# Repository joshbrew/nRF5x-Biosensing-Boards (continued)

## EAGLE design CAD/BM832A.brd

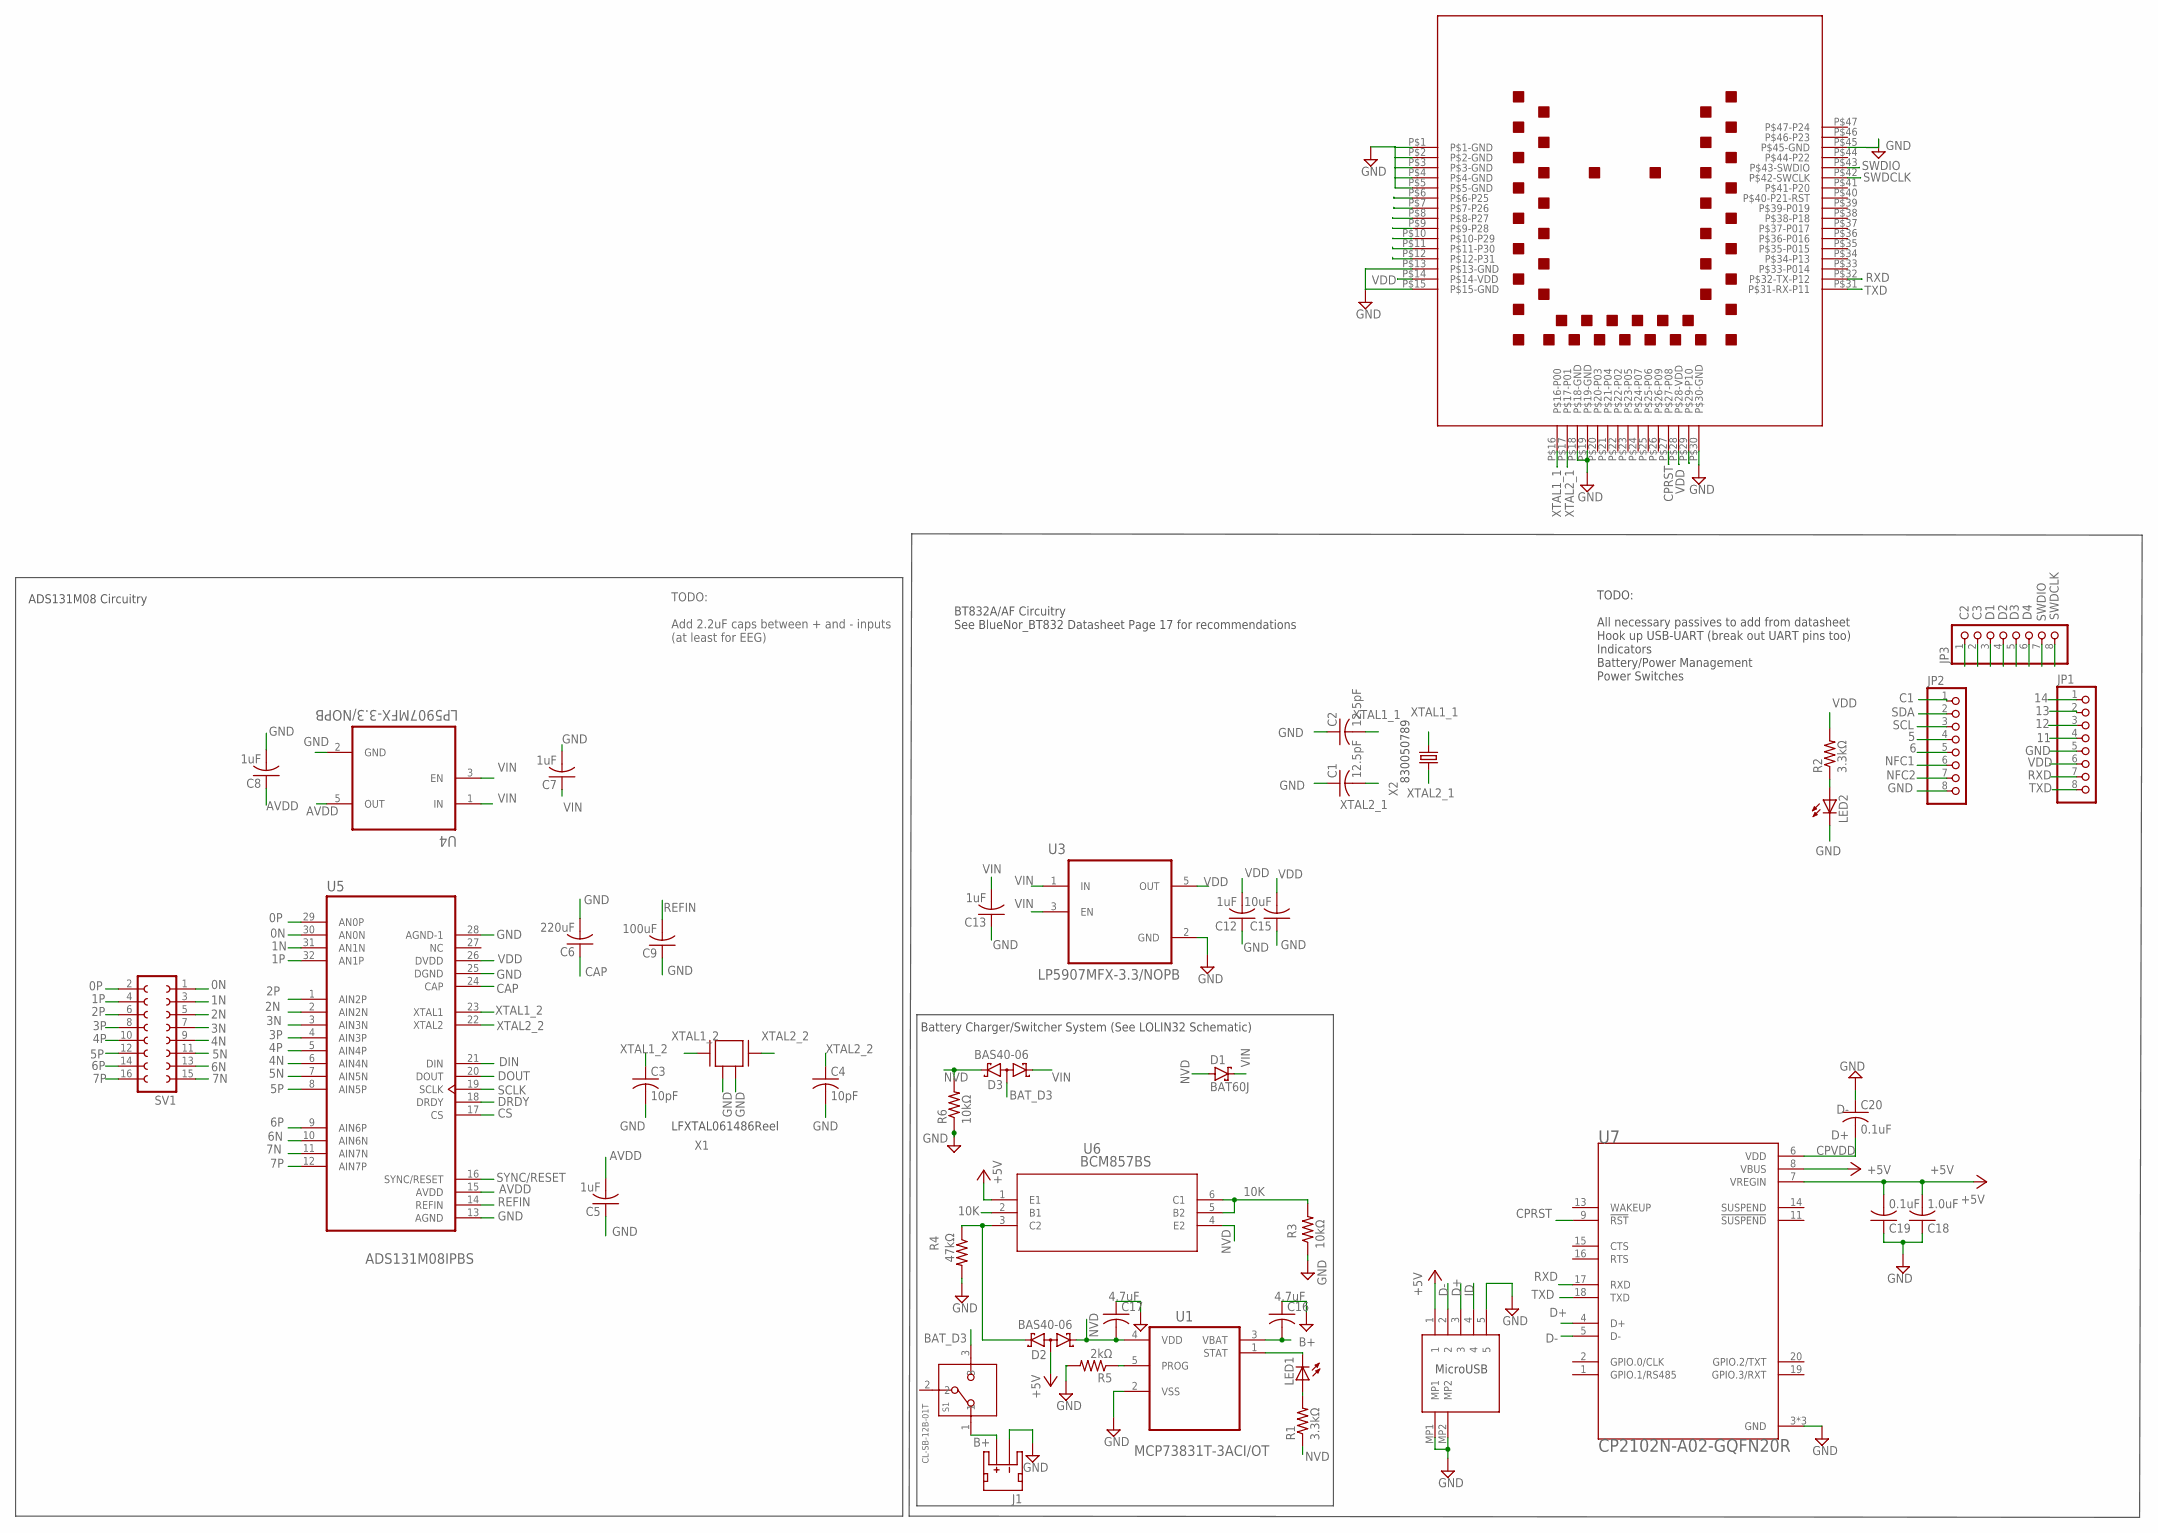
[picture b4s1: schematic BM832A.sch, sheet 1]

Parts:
C1, C2: 12.5pF; C0402
C3, C4: 10pF; C0402
C5, C7, C8, C12, C13: 1uF; C0402
C6: 220uF; C0402
C9: 100uF; C0402
C15: 10uF; C0402
C16, C17: 4.7uF; C0402
C18: 1.0uF; C0402
C19, C20: 0.1uF; C0402
D1: BAT60J; SOD323_ST
D2, D3: BAS40-06; SOT23
J1: JST_2MM_MALE; JST-2-SMD
JP1, JP2, JP3: PINHD-1X8CLEANBIG; 1X08-CLEANBIG
LED1, LED2: LEDCHIP-LED0603; CHIP-LED0603
R1, R2: 3.3kΩ; R0402
R3, R6: 10kΩ; R0402
R4: 47kΩ; R0402
R5: 2kΩ; R0402
S1: CL-SB-12B-01T; CL-SB-12B
SV1: FE08-2
U1: MCP73831T-3ACI/OT; SOT95P270X145-5N
U3, U4: LP5907MFX-3.3/NOPB; SOT95P280X145-5N
U5: ADS131M08IPBS; QFP50P700X700X120-32N
U6: BCM857BS; SOT363_NEX
U7: CP2102N-A02-GQFN20R; SILABS_CP2102N-A02-GQFN20R
U8: BM832
U$1: DX4R005JJ2R1800
X1: ABM3B-8.000MHZ-B2-T
X2: FC-12M

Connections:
0N: SV1.1, U5.30 (AN0N)
0P: SV1.2, U5.29 (AN0P)
1N: SV1.3, U5.31 (AN1N)
1P: SV1.4, U5.32 (AN1P)
2N: SV1.5, U5.2 (AIN2N)
2P: SV1.6, U5.1 (AIN2P)
3N: SV1.7, U5.3 (AIN3N)
3P: SV1.8, U5.4 (AIN3P)
4N: SV1.9, U5.6 (AIN4N)
4P: SV1.10, U5.5 (AIN4P)
5: JP2.4
5N: SV1.11, U5.7 (AIN5N)
5P: SV1.12, U5.8 (AIN5P)
6: JP2.5
6N: SV1.13, U5.10 (AIN6N)
6P: SV1.14, U5.9 (AIN6P)
7N: SV1.15, U5.11 (AIN7N)
7P: SV1.16, U5.12 (AIN7P)
10K: R3.2, U6.2 (B1), U6.5 (B2), U6.6 (C1)
11: JP1.4
12: JP1.3
13: JP1.2
14: JP1.1
+5V: C18.2, C19.2, D2.3 (AA), U6.1 (E1), U7.7 (VREGIN), U7.8 (VBUS), U$1.1
AVDD: C5.2, C8.1, U4.5 (OUT), U5.15 (AVDD)
B+: C16.2, J1.2 (+), S1.1, U1.3 (VBAT)
BAT_D3: D3.3 (AA), S1.3
C1: JP2.1
C2: JP3.1
C3: JP3.2
CAP: C6.1, U5.24 (CAP)
CPRST: U7.9 (!RST), U8.P$27 (P$27-P08)
CPVDD: C20.2, U7.6 (VDD)
CS: U5.17 (CS)
D1: JP3.3
D2: JP3.4
D3: JP3.5
D4: JP3.6
D+: U7.4 (D+), U$1.3
D-: U7.5 (D-), U$1.2
DIN: U5.21 (DIN)
DOUT: U5.20 (DOUT)
DRDY: U5.18 (DRDY)
GND: C1.1, C2.1, C3.2, C4.2, C5.1, C6.2, C7.2, C8.2, C9.1, C12.1, C13.1, C15.1, C16.1, C17.1, C18.1, C19.1, C20.1, J1.1 (-), JP1.5, JP2.8, LED2.C, R3.1, R4.2, R5.2, R6.1, U1.2 (VSS), U3.2 (GND), U4.2 (GND), U5.13 (AGND), U5.25 (DGND), U5.28 (AGND-1), U7.3 (GND), U7.12 (GND), U7.21 (GND), U8.P$1 (P$1-GND), U8.P$2 (P$2-GND), U8.P$3 (P$3-GND), U8.P$4 (P$4-GND), U8.P$5 (P$5-GND), U8.P$13 (P$13-GND), U8.P$18 (P$18-GND), U8.P$19 (P$19-GND), U8.P$30 (P$30-GND), U8.P$45 (P$45-GND), U$1.5, U$1.MP1, U$1.MP2, X1.2, X1.4
ID: U$1.4
unnamed: LED2.A, R2.1
unnamed: R5.1, U1.5 (PROG)
unnamed: LED1.A, R1.2
unnamed: D2.2 (K2), R4.1, U6.3 (C2)
unnamed: LED1.C, U1.1 (STAT)
NFC1: JP2.6
NFC2: JP2.7
NVD: C17.2, D1.A, D2.1 (K1), D3.2 (K2), R1.1, R6.2, U1.4 (VDD), U6.4 (E2)
REFIN: C9.2, U5.14 (REFIN)
RXD: JP1.7, U7.17 (RXD), U8.P$32 (P$32-TX-P12)
SCL: JP2.3
SCLK: U5.19 (SCLK)
SDA: JP2.2
SWDCLK: JP3.8, U8.P$42 (P$42-SWCLK)
SWDIO: JP3.7, U8.P$43 (P$43-SWDIO)
SYNC/RESET: U5.16 (SYNC/RESET)
TXD: JP1.8, U7.18 (TXD), U8.P$31 (P$31-RX-P11)
VDD: C12.2, C15.2, JP1.6, R2.2, U3.5 (OUT), U5.26 (DVDD), U8.P$14 (P$14-VDD), U8.P$28 (P$28-VDD)
VIN: C7.1, C13.2, D1.C, D3.1 (K1), U3.1 (IN), U3.3 (EN), U4.1 (IN), U4.3 (EN)
XTAL1_1: C2.2, U8.P$16 (P$16-P00), X2.2
XTAL1_2: C3.1, U5.23 (XTAL1), X1.1
XTAL2_1: C1.2, U8.P$17 (P$17-P01), X2.1
XTAL2_2: C4.1, U5.22 (XTAL2), X1.3

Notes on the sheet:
LFXTAL061486Reel
830050789
MicroUSB
TODO: Add 2.2uF caps between + and - inputs (at least for EEG)
Battery Charger/Switcher System (See LOLIN32 Schematic)
ADS131M08 Circuitry
BT832A/AF Circuitry See BlueNor_BT832 Datasheet Page 17 for recommendations
TODO: All necessary passives to add from datasheet Hook up USB-UART (break out UART pins too) Indicators Battery/Power Management Power Switches

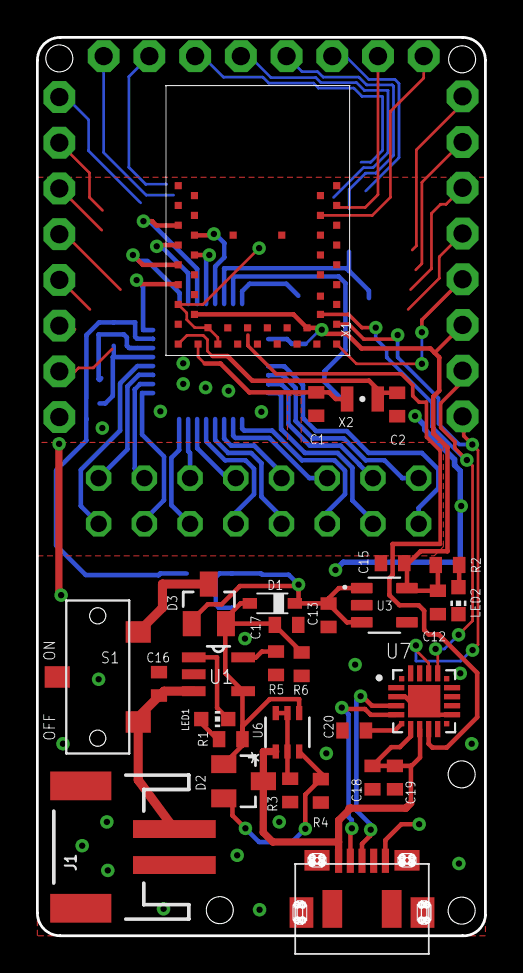
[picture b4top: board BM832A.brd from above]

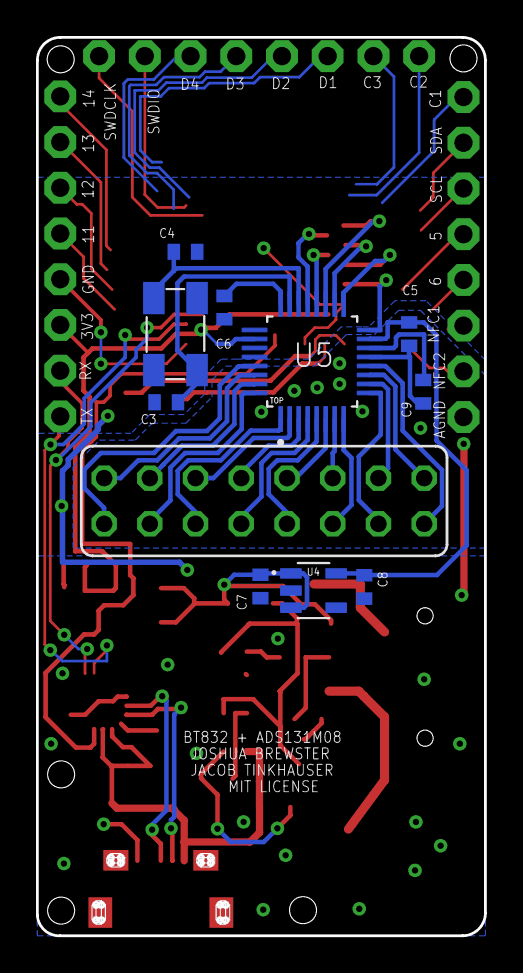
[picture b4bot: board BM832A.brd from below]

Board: 2 copper layers, 24.9 x 49.9 mm, 44 parts (11 on the bottom side), 44 nets.
